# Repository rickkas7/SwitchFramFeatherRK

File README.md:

# SwitchFramFeatherRK

*Demo FeatherWing with DIP and BCD switches, and FRAM non-volatile memory*

This project is a simple Adafruit FeatherWing that includes things you might want to include on a board or wing you design:

- DIP switch
- BCD rotary switch
- FRAM (ferro-electric non-volatile memory)

You might use this for configuration of your project, for example.

While the Eagle CAD files and BOM (bill of materials) are included here so you can build your own board exactly like this one, it's really intended to be ideas for things you can include in your own designs.

The other handy thing is that all of the features connected by I2C (pins D0 and D1), so it requires no additional GPIO! 

## Switches

Sometimes you'll want to include physical switches on your board. This demo includes two kinds:

- 4 on-off SPST DIP switches
- A rotary selector that supports values 0-9 by turning the knob

One problem with these types of switches is that they require a lot of GPIO pins. Each requires 4, so rather than tie up 8 GPIO pins on the Argon/Boron/Xenon, an 8-port I2C GPIO expander is used.

The MCP23008 I2C GPIO expander is great for situations like this. It attaches to the I2C bus (pins D0 and D1) and you can include up to 8 of these chips on a single device.

On the left side of the FeatherWing (as pictured above) you'll notice 3 small solder jumpers labeled A0, A1, and A2. By shorting out the solder jumper you can change the I2C address of the MCP23008 chip.

To make this board flexible, the solder jumpers connect to VCC (shorting the jumper sets value 1) and there are 10K pull-down resistors on the address lines. On your own boards you may want to just hardcode the address lines and eliminate the resistors and solder jumpers.

| A2 | A1 | A0 | Address |
| --- | --- | --- | --- | 
| open | open | open | 0x20 |
| open | open | closed  | 0x21 |
| open | closed | open | 0x22 |
| open | closed | closed | 0x23 |
| closed | open | open | 0x24 |
| closed | open | closed  | 0x25 |
| closed | closed | open | 0x26 |
| closed | closed | closed | 0x27 |

The [MCP23008-RK](https://github.com/rickkas7/MCP23008-RK) library is used to read the GPIO lines connected to the chip.

## FRAM

The FRAM (Ferroelectric RAM) is a non-volatile storage device, meaning it keeps the values when power is removed. Unlike flash memory, it's fast to write to and does not wear out, so it's ideal for saving values frequently.

The chip included here is a Fujitsu MB85RC64TAPNF-G-BDERE1, IC FRAM 64K I2C 3.4MHZ 8SOP. It costs $ 1.58 at single quantities so it's affordable to add to your board. It's also tiny, in an 8-SOP package, and connects by I2C, so it doesn't need extra GPIO. That 64 Kbits, so it can store 8 Kbytes of data.

On the right side of the FeatherWing (as pictured above) you'll notice 3 small solder jumpers labeled A0, A1, and A2. By shorting out the solder jumper you can change the I2C address of the FRAM chip.

| A2 | A1 | A0 | Address |
| --- | --- | --- | --- | 
| open | open | open | 0x50 |
| open | open | closed  | 0x51 |
| open | closed | open | 0x52 |
| open | closed | closed | 0x53 |
| closed | open | open | 0x54 |
| closed | open | closed  | 0x55 |
| closed | closed | open | 0x56 |
| closed | closed | closed | 0x57 |

The [MB85RC256V-FRAM-RK](https://github.com/rickkas7/MB85RC256V-FRAM-RK) library makes it easy to use this chip. It provides an API just like the Particle [EEPROM API](https://docs.particle.io/reference/device-os/firmware/#eeprom) to load and save values in the FRAM.

## Sample Code

The sample program prints out the the status of the switches at startup and when the values change. The library takes care of debouncing the switches and reporting changes automatically.

The sample code also stores a counter in FRAM, and the counter is updated once per second.

```
0000005678 [app] INFO: onDipSwitchChange oooo
0000005680 [app] INFO: onBcdSwitchChange 6
0000005684 [app] INFO: counter=908
...
0000015683 [app] INFO: counter=918
0000016093 [app] INFO: onBcdSwitchChange 7
0000016683 [app] INFO: counter=919
0000017683 [app] INFO: counter=920
0000018026 [app] INFO: onBcdSwitchChange 8
0000018684 [app] INFO: counter=921
0000019684 [app] INFO: counter=922
0000019883 [app] INFO: onBcdSwitchChange 7
0000020684 [app] INFO: counter=923
0000021157 [app] INFO: onBcdSwitchChange 6
...
0000028683 [app] INFO: counter=931
0000029289 [app] INFO: onDipSwitchChange |ooo
0000029684 [app] INFO: counter=932
0000030684 [app] INFO: counter=933
0000031684 [app] INFO: counter=934
0000032684 [app] INFO: counter=935
0000033684 [app] INFO: counter=936
0000034217 [app] INFO: onDipSwitchChange oooo
```

You must call from setup:

```
	switchFramFeather.setup();
```

And from loop:

```
	switchFramFeather.loop();
```

This provides time to the library to process the switches.

If you're not familiar with C++11 lambda syntax, this might look peculiar, but it's not that complicated:

```
	switchFramFeather.onBcdSwitchChange( {
		Log.info("onBcdSwitchChange %d", value);
	});
```

What this does is register a function to be called when the BCD switch value changes. It's just that it's declared in-line using a lambda, rather than having to declare a separate function. 

The Log.info statement will execute and log to debug serial whenever the switch changes (even after setup exits).

The sample code to use the FRAM looks like this:

```
if (millis() - lastCounterUpdate >= 1000) {
		lastCounterUpdate = millis();

		size_t counter;
		switchFramFeather.get(0, counter);
		counter++;
		switchFramFeather.put(0, counter);

		Log.info("counter=%u", counter);
	}
```

## BOM and Assembly

| Quantity | Description | Example | 
| --- | --- | --- |
| 8 | 10K resistor 0603 | [Panasonic ERJ-PA3J103V](https://www.digikey.com/product-detail/en/panasonic-electronic-components/ERJ-PA3J103V/P10KBZCT-ND/5036237) |
| 1 | DIP switch SPST 4 pos | [CTS Electrocomponents 209-4MS](https://www.digikey.com/product-detail/en/cts-electrocomponents/209-4MS/CT2094MS-ND/217664) |
| 1 | DIP Switch BCD 10 Position | [CTS Electrocomponents 220ADC10](https://www.digikey.com/product-detail/en/220ADC10/CT3069-ND/4743855/?itemSeq=273765935) |
| 1 | MCP23008 | [Microchip MCP23008T-E-SO](https://www.digikey.com/product-detail/en/microchip-technology/MCP23008T-E-SO/MCP23008T-E-SOCT-ND/5358243) |
| 1 | IC FRAM 64K I2C 3.4MHZ 8SOP | [Fujitsu MB85RC64TAPNF-G-BDERE1](https://www.digikey.com/product-detail/en/fujitsu-electronics-america-inc/MB85RC64TAPNF-G-BDERE1/865-1274-1-ND/6802280) |
| | Male header pins 0.1" | [Sullins PRPC040SAAN-RC](https://www.digikey.com/product-detail/en/PRPC040SAAN-RC/S1011EC-40-ND/2775214) |

The Eagle CAD files are included in the Github repository. I fabricated my boards at [OshPark](https://oshpark.com). It costs $9 to get 3 FeatherWing boards manufactured (standard speed), with free shipping (in the United States, at least). The other handy thing is that you can upload the .brd file directly and don't have to generate Gerber files.

And while theoretically possible to build this board using solder paste and a soldering iron with a very steady hand, it's intended to be reflowed. I use an inexpensive [T962 Reflow Oven](https://www.amazon.com/SMTHouse-Infrared-Soldering-Machine-Automatic/dp/B0152FTXN2/ref=sr_1_4).

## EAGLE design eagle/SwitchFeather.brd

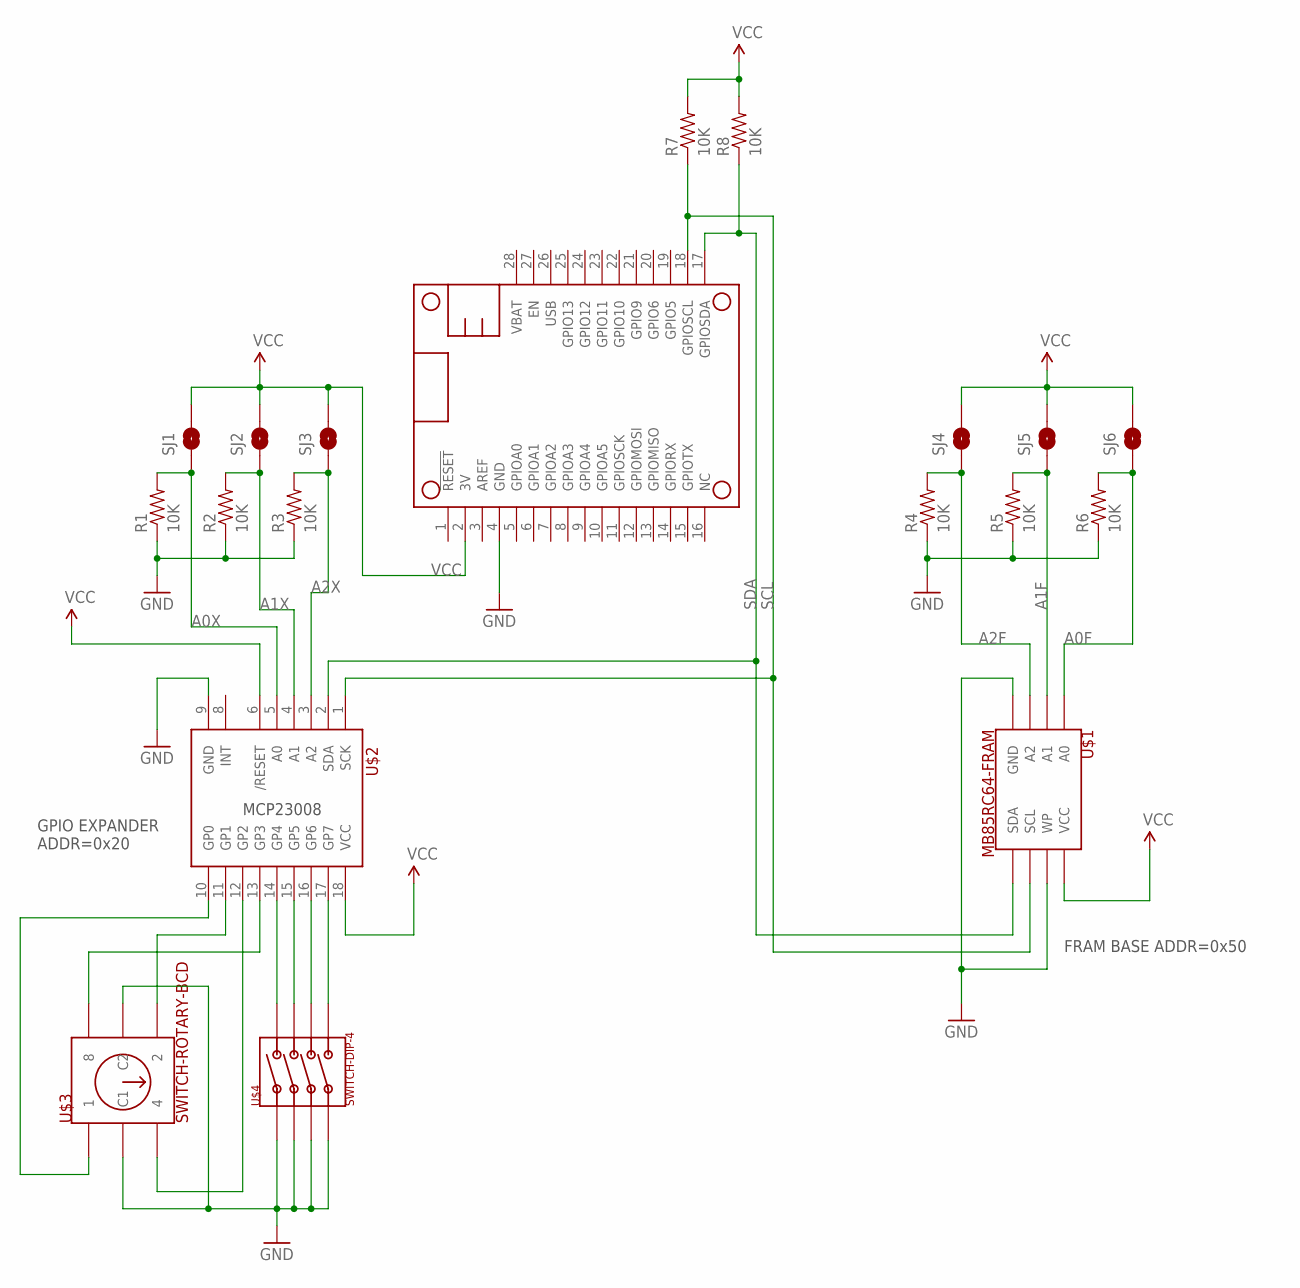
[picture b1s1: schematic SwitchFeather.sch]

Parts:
MS1: FEATHERWING
R1, R2, R3, R4, R5, R6, R7, R8: 10K; 0603-RES
SJ1, SJ2, SJ3, SJ4, SJ5, SJ6: JUMPER-PAD-2-NO; PAD-JUMPER-2-NO_NO_SILK
U$1: MB85RC64-FRAM; 8-SOIC-MAXIM
U$2: MCP23008; SOIC-18-W-MAXIM
U$3: SWITCH-ROTARY-BCD
U$4: SWITCH-DIP-4

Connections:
A0F: R6.2, SJ6.1, U$1.1 (A0)
A0X: R1.2, SJ1.1, U$2.5 (A0)
A1F: R5.2, SJ5.1, U$1.2 (A1)
A1X: R2.2, SJ2.1, U$2.4 (A1)
A2F: R4.2, SJ4.1, U$1.3 (A2)
A2X: R3.2, SJ3.1, U$2.3 (A2)
GND: MS1.4 (GND), R1.1, R2.1, R3.1, R4.1, R5.1, R6.1, U$1.4 (GND), U$1.7 (WP), U$2.9 (GND), U$3.P$2 (C1), U$3.P$5 (C2), U$4.P$1 (1), U$4.P$3 (3), U$4.P$5 (5), U$4.P$7 (7)
GP0: U$2.10 (GP0), U$3.P$1 (1)
GP1: U$2.11 (GP1), U$3.P$4 (2)
GP2: U$2.12 (GP2), U$3.P$3 (4)
GP3: U$2.13 (GP3), U$3.P$6 (8)
GP4: U$2.14 (GP4), U$4.P$2 (2)
GP5: U$2.15 (GP5), U$4.P$4 (4)
GP6: U$2.16 (GP6), U$4.P$6 (6)
GP7: U$2.17 (GP7), U$4.P$8 (8)
SCL: MS1.18 (GPIOSCL), R7.1, U$1.6 (SCL), U$2.1 (SCK)
SDA: MS1.17 (GPIOSDA), R8.1, U$1.5 (SDA), U$2.2 (SDA)
VCC: MS1.2 (3V), R7.2, R8.2, SJ1.2, SJ2.2, SJ3.2, SJ4.2, SJ5.2, SJ6.2, U$1.8 (VCC), U$2.6 (/RESET), U$2.18 (VCC)

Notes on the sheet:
FRAM BASE ADDR=0x50
MCP23008
GPIO EXPANDER ADDR=0x20

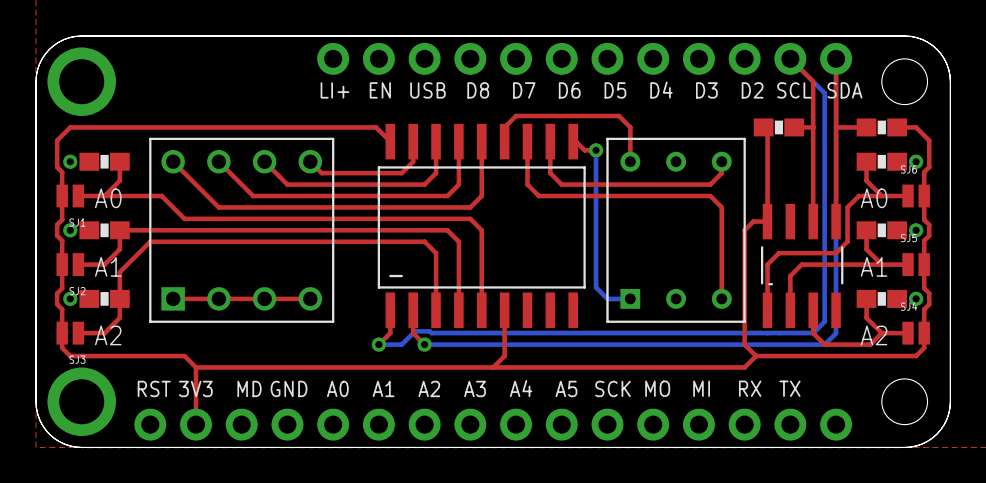
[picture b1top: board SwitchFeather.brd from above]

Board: 2 copper layers, 50.8 x 22.9 mm, 19 parts (0 on the bottom side), 18 nets.

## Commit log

2019-02-06 Initial Version
2019-02-06 fix travis build
2019-02-06 fix travis build #2
